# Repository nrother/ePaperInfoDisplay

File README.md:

# ePaper Info Display

A wireless, battery-powered ePaper Display that shows you important information at a glance.
Inspired by [a similiar project](https://spritesmods.com/?art=einkdisplay) by spritesmods.

A [7.4' ePaper Display from PervasiveDisplays](https://www.pervasivedisplays.com/product/7-4-e-ink-displays/) is used as the display.
It is powered by ESP32-C3 WiFi-enabled microcontroller.
The microcontroller wakes up every 24 hours and updates the e-paper display with an 800x480 image downloaded from a server.
On the server side, a Python script generates the image, showing a calendar, the weather forecast, and the next appointments.

This repository contains the hardware, firmware and software for the project.

## Hardware

The `hardware/` folder contains all schematics and PCB layouts in KiCAD format.

### Changelog

#### Rev. 3

- Fixed swapped USB DP+/-, USB usable again
- Fixed swapped labels USR1/USR2
- Add resistor divider for VBAT_SENSE to avoid excessive voltage on GPIO pin
- WAKEUP button changed to BOOT (connected to GPIO9)
- VBAT_SENSE moved to GPIO4 which has a usable ADC
- GPIO association of some signals changed to avoid issues strapping pins:
	- LED1 now on GPIO5
	- LED2 now on GPIO6
	- /BUSY now on GPIO7
	- /PWR_EN now on GPIO8

##### Known issues

None

#### Rev.2 (only usable with fixes)
- Use bottom-connect FPC connector
- Mirror some parts of the layout

##### Known issues
- USB DP+/- is switched
- #BUSY of Display is connected to GPIO9, which causes the chip to enter the Bootloader every time
- VBAT_SENSE is on ADC2_CH0 which is not usable when WiFi is active
- Labels USR1/USR2 are switched
- GPIO8 and GPIO2 (which are strapping pins) are used otherwise
- The WAKEUP button is useless (one can just use RESET), but a boot button would have been nice

#### Rev.1 (broken)
- First revision

##### Known issues
- Orientation/Location of ePaper FPC connector is wrong

## Firmware

The firmware can be found in the `firmware/` folder.
It is based on [ESPHome](https://esphome.io/).

To get started:
```shell
cd firmware/
python3 -m venv .venv
. .venv/bin/activate
pip install -r requirements.txt
cp secrets.example.yaml secrets.yaml
vim secrets.yaml
esphome compile epaperinfodisplay.yaml
esphome upload epaperinfodisplay.yaml
```

There is a ESPHome-compatible custom component for the e-paper display from Pervasive Displays in `esphome/`.
This might also be useful outside this project.

## Software

The host software is writting in Python using [Flask](https://flask.palletsprojects.com/en/stable/).
It must run on some kind of server, like a Raspberry Pi or a NAS.

To get started:
```shell
cd software/
python3 -m venv .venv
. .venv/bin/activate
pip install -r requirements.txt
cp config.example.yaml config.yaml
vim config.yaml
flask run --host 0.0.0.0 # make accessible from outside localhost
```

Weather data is fetched from [OpenMeteo](https://open-meteo.com/).
For this to work you need to specify your location in the `config.yaml` file.
Calendar appointments are fetched from a CalDAV server.
The example configuration contains the correct path for [Baïkal](https://sabre.io/baikal/), but any kind of CalDAV server should work.
You might need to find out the correct path for your server.

## License

MIT

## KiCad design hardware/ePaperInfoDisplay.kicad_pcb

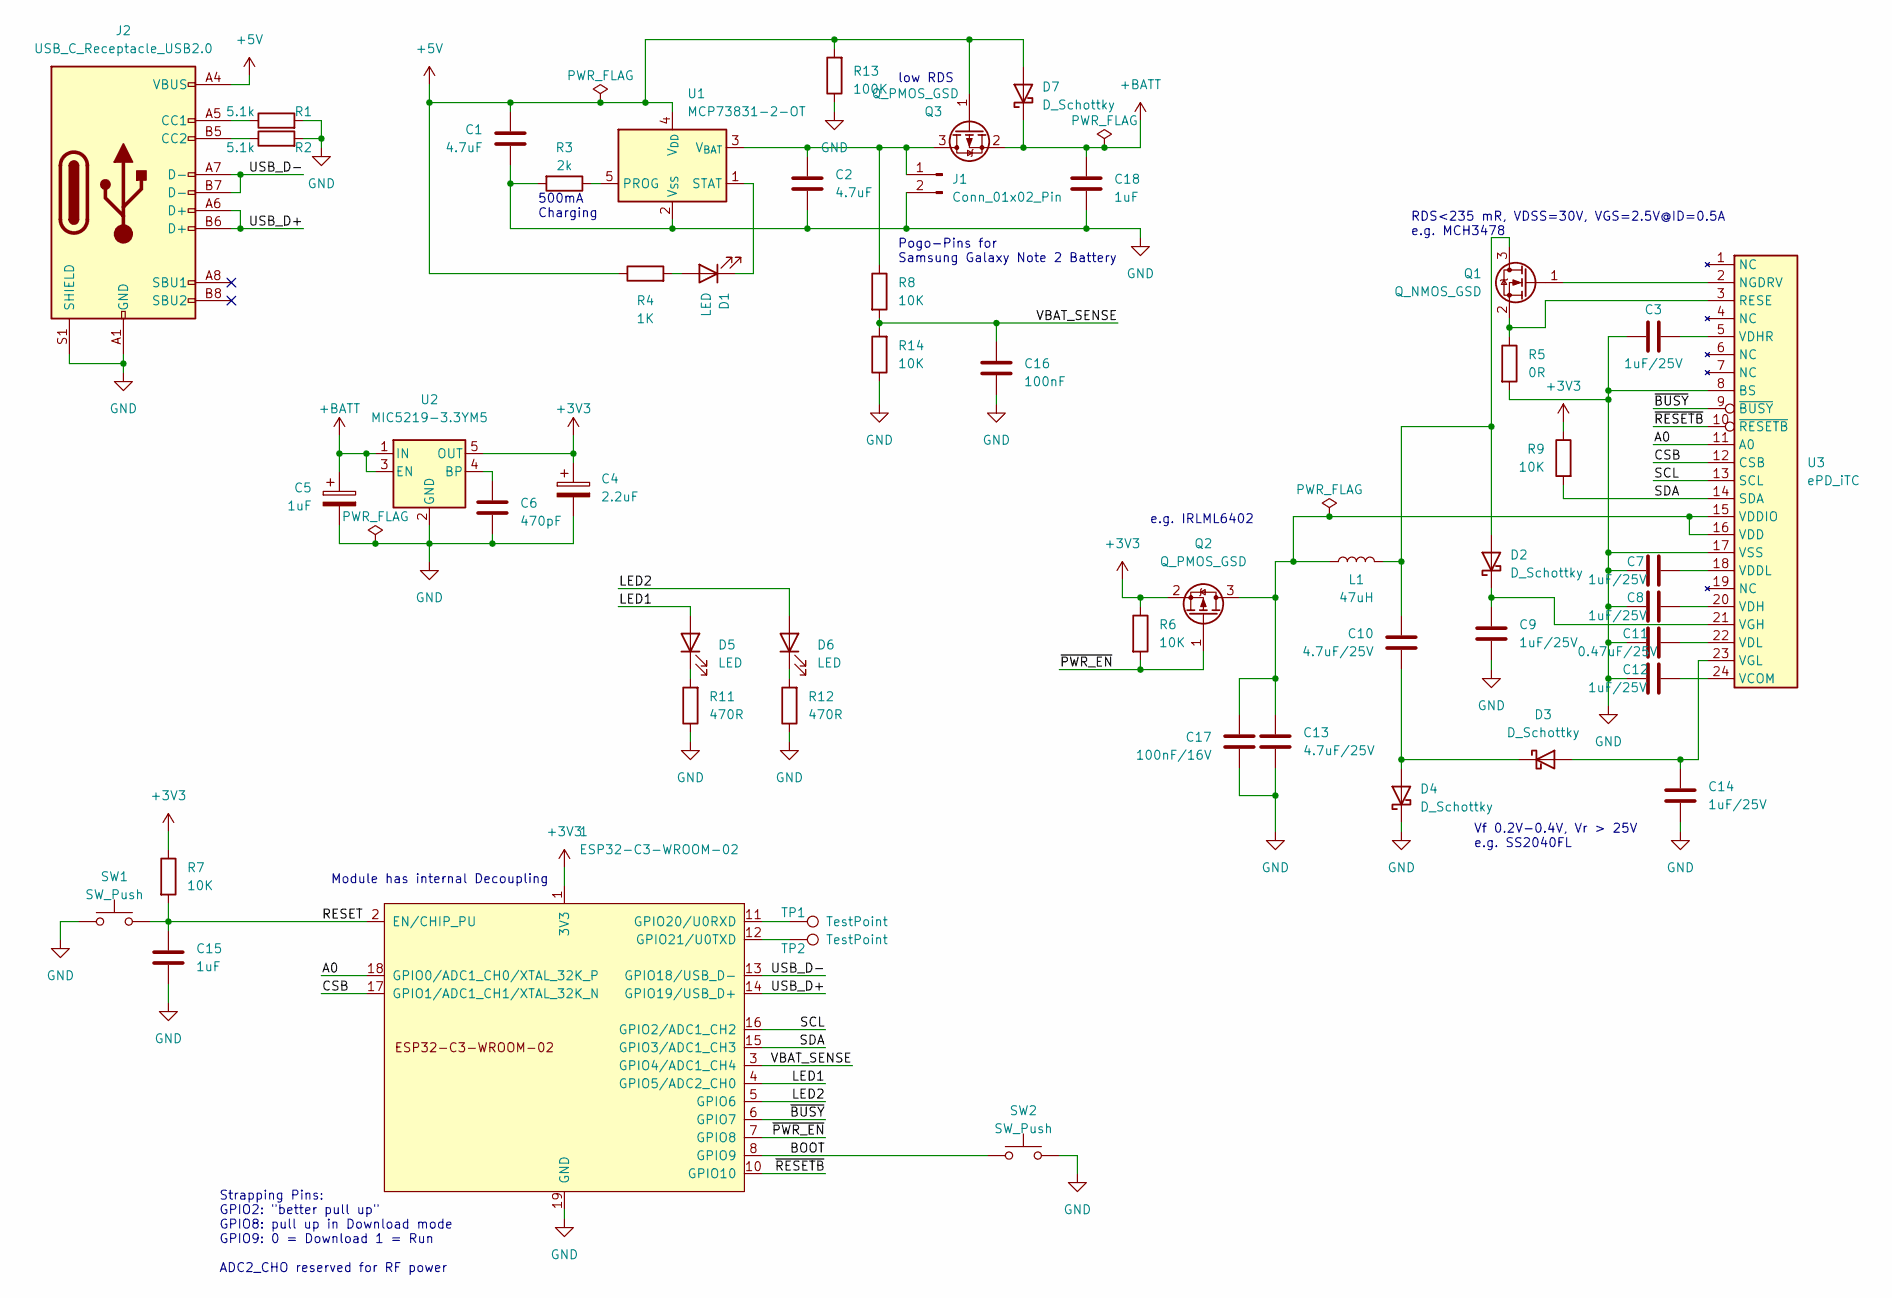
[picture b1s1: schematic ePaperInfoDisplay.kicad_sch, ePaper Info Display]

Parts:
1: ESP32-C3-WROOM-02
C1, C2: 4.7uF; C_0805_2012Metric_Pad1.18x1.45mm_HandSolder
C3, C7, C8, C9, C12, C14: 1uF/25V; C_0805_2012Metric_Pad1.18x1.45mm_HandSolder
C4: 2.2uF; C_0805_2012Metric_Pad1.18x1.45mm_HandSolder
C5, C15, C18: 1uF; C_0805_2012Metric_Pad1.18x1.45mm_HandSolder
C6: 470pF; C_0805_2012Metric_Pad1.18x1.45mm_HandSolder
C10, C13: 4.7uF/25V; C_0805_2012Metric_Pad1.18x1.45mm_HandSolder
C11: 0.47uF/25V; C_0805_2012Metric_Pad1.18x1.45mm_HandSolder
C16: 100nF; C_0805_2012Metric_Pad1.18x1.45mm_HandSolder
C17: 100nF/16V; C_0805_2012Metric_Pad1.18x1.45mm_HandSolder
D1, D5, D6: LED; LED_0805_2012Metric_Pad1.15x1.40mm_HandSolder
D2, D3, D4, D7: D_Schottky; D_SOD-123F
J1: Conn_01x02_Pin; PinHeader_1x02_P2.54mm_Vertical
J2: USB_C_Receptacle_USB2.0; USB_C_Receptacle_GCT_USB4105-xx-A_16P_TopMnt_Horizontal
L1: 47uH; L_7.3x7.3_H4.5
Q1: Q_NMOS_GSD; SOT-323_SC-70_Handsoldering
Q2, Q3: Q_PMOS_GSD; SOT-323_SC-70_Handsoldering
R1, R2: 5.1k; R_0805_2012Metric_Pad1.20x1.40mm_HandSolder
R3: 2k; R_0805_2012Metric_Pad1.20x1.40mm_HandSolder
R4: 1K; R_0805_2012Metric_Pad1.20x1.40mm_HandSolder
R5: 0R; R_0805_2012Metric_Pad1.20x1.40mm_HandSolder
R6, R7, R8, R9, R14: 10K; R_0805_2012Metric_Pad1.20x1.40mm_HandSolder
R11, R12: 470R; R_0805_2012Metric_Pad1.20x1.40mm_HandSolder
R13: 100K; R_0805_2012Metric_Pad1.20x1.40mm_HandSolder
SW1, SW2: SW_Push; SW_PUSH_6mm
TP1, TP2: TestPoint; TestPoint_Pad_D1.0mm
U1: MCP73831-2-OT; SOT-23-5_HandSoldering
U2: MIC5219-3.3YM5; SOT-23-5_HandSoldering
U3: ePD_iTC; TE_2-1734592-4_1x24-1MP_P0.5mm_Horizontal

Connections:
+3V3: 1.1 (3V3), C4.1, Q2.2 (S), R6.1, R7.1, R9.1, U2.5 (OUT)
+5V: C1.1, D7.2 (A), J2.A4 (VBUS), J2.A9 (VBUS), J2.B4 (VBUS), J2.B9 (VBUS), Q3.1 (G), R4.1, R13.2, U1.4 (V_{DD})
+BATT: C5.1, C18.1, D7.1 (K), Q3.2 (S), U2.1 (IN), U2.3 (EN)
/A0: 1.18 (GPIO0/ADC1_CH0/XTAL_32K_P), U3.11 (A0)
/BOOT: 1.8 (GPIO9), SW2.2
/CSB: 1.17 (GPIO1/ADC1_CH1/XTAL_32K_N), U3.12 (CSB)
/LED1: 1.4 (GPIO5/ADC2_CH0), D5.2 (A)
/LED2: 1.5 (GPIO6), D6.2 (A)
/RESET: 1.2 (EN/CHIP_PU), C15.1, R7.2, SW1.2
/SCL: 1.16 (GPIO2/ADC1_CH2), U3.13 (SCL)
/SDA: 1.15 (GPIO3/ADC1_CH3), R9.2, U3.14 (SDA)
/USB_D+: 1.14 (GPIO19/USB_D+), J2.A6 (D+), J2.B6 (D+)
/USB_D-: 1.13 (GPIO18/USB_D-), J2.A7 (D-), J2.B7 (D-)
/VBAT_SENSE: 1.3 (GPIO4/ADC1_CH4), C16.1, R8.2, R14.2
/~BUSY: 1.6 (GPIO7), U3.9 (~BUSY)
/~PWR_EN: 1.7 (GPIO8), Q2.1 (G), R6.2
/~RESETB: 1.10 (GPIO10), U3.10 (~RESETB)
GND: 1.9 (GND), 1.19 (GND), C1.2, C2.2, C3.1, C4.2, C5.2, C6.2, C7.1, C8.1, C9.2, C11.1, C12.1, C13.2, C14.2, C15.2, C16.2, C17.2, C18.2, D4.1 (K), J1.2, J2.A1 (GND), J2.A12 (GND), J2.B1 (GND), J2.B12 (GND), J2.S1 (SHIELD), R1.2, R2.2, R3.2, R5.2, R11.1, R12.1, R13.1, R14.1, SW1.1, SW2.1, U1.2 (V_{SS}), U2.2 (GND), U3.8 (BS), U3.17 (VSS)
unnamed: 1.11 (GPIO20/U0RXD), TP1.1
unnamed: 1.12 (GPIO21/U0TXD), TP2.1
unnamed: D1.2 (A), R4.2
unnamed: D1.1 (K), U1.1 (STAT)
unnamed: C10.1, D2.2 (A), L1.2, Q1.3 (D)
unnamed: C9.1, D2.1 (K), U3.21 (VGH)
unnamed: C14.1, D3.2 (A), U3.23 (VGL)
unnamed: C10.2, D3.1 (K), D4.2 (A)
unnamed: D5.1 (K), R11.2
unnamed: D6.1 (K), R12.2
unnamed: C2.1, J1.1, Q3.3 (D), R8.1, U1.3 (V_{BAT})
unnamed: J2.A5 (CC1), R1.1
unnamed: J2.B5 (CC2), R2.1
unnamed: Q1.1 (G), U3.2 (NGDRV)
unnamed: Q1.2 (S), R5.1, U3.3 (RESE)
unnamed: C13.1, C17.1, L1.1, Q2.3 (D), U3.15 (VDDIO), U3.16 (VDD)
unnamed: R3.1, U1.5 (PROG)
unnamed: C6.1, U2.4 (BP)
unnamed: C12.2, U3.24 (VCOM)
unnamed: C7.2, U3.18 (VDDL)
unnamed: C8.2, U3.20 (VDH)
unnamed: C3.2, U3.5 (VDHR)
unnamed: C11.2, U3.22 (VDL)

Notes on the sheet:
500mA Charging
Module has internal Decoupling
low RDS
Pogo-Pins for Samsung Galaxy Note 2 Battery
e.g. IRLML6402
RDS<235 mR, VDSS=30V, VGS=2.5V@ID=0.5A e.g. MCH3478
Vf 0.2V-0.4V, Vr > 25V e.g. SS2040FL
Strapping Pins: GPIO2: "better pull up" GPIO8: pull up in Download mode GPIO9: 0 = Download 1 = Run ADC2_CHO reserved for RF power

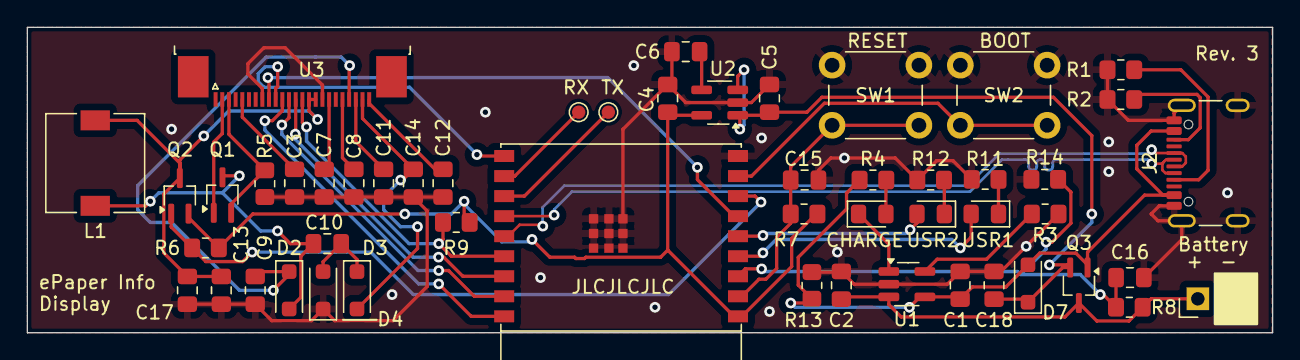
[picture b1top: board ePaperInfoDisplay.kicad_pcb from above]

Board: 2 copper layers, 93.2 x 22.9 mm, 52 parts (0 on the bottom side), 41 nets.

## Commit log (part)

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2024-01-06 Update gitignore
2024-01-06 Add Revision 2
    Use Bottom-connect FPC connector, mirror some parts of the layout
2025-06-26 Move KiCAD files to hardware/
2025-06-26 Add support for ePaper displays form Pervasive Displays
2025-06-26 Update Pervasive Displays driver to follow the app note more closely
2025-06-26 Add firmware configuration (using ESPHome)
2025-06-26 Add first version of host software
2025-06-28 Add spline interpolation to the temperature curve
2025-06-30 Add deep sleep to firmware
2025-06-30 Update README and .gitignores, add LICENSE
2025-08-18 Update WMO code mapping for weather icons
    Now based on https://open-meteo.com/en/docs#weather_variable_documentation
2025-08-18 Improve software
    - Split image generation and retrival to speed up the latter
    - Add support for special images on some days
    - Always show 10 calendar lines
    - Some layout tweaks
2025-08-18 Add GitHub Actions workflow for building and publishing Docker image
2025-08-18 Fix docker image generation: A lowercase name is required
2025-08-18 Fix GH Actions workflow again
    Don't trust the AI, the pipe operator is not a thing here!
2025-08-18 Add Dockerfile, move config to /config
2025-08-18 Add push: true to workflow
2025-08-18 Add SegoeUI font to docker image
    Yeah, very official download, I know...
2025-08-18 Add required wget and fontconfig
2025-08-18 Set German locale in Dockerfile
2025-08-18 Better approach to setting german locale
2025-08-19 Add locale to /etc/locale.gen so that is acutally build
2025-08-20 Update PCB to KiCAD 9
2025-08-23 Add error handler for image generation
2025-08-23 Add missing "showers" icon, remove unused icons
2025-08-23 Use UTC time for finding events
    This prevents events from yesterday beeing returned if update are done right after midnight. See https://github.com/python-caldav/caldav/issues/351
2025-08-23 Software cleanup
2025-08-23 Only update containers if software/ changed
2025-08-23 Show an error message if image download fails in the firmware
2025-09-01 Update hardware to Rev. 3
    Fixed all of the known issues:
    - Fixed swapped USB DP+/-, USB usable again
    - Fixed swapped labels USR1/USR2
    - Add resistor divider for VBAT_SENSE to avoid excessive voltage on GPIO pin
    - WAKEUP button changed to BOOT (connected to GPIO9)
    - VBAT_SENSE moved to GPIO4 which has a usable ADC
2025-10-01 Minor UI improvements
2025-10-01 Make the firmware request the next wakeup time instead of sleeping always 24h
2026-01-11 Fix mapping of WMO code 48: Rime fog
2026-06-01 In debug mode, re-generate image for every request
2026-06-01 Tweak layout
2026-06-01 Show rain-chart and weather for next three days
2026-06-07 Fix scale factor of rain chart
    50mm/h of rain would be *a lot* ;)

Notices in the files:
hardware/ePaperInfoDisplay.kicad_pcb:
© 2025
